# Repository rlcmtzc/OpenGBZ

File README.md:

&emsp;&emsp;&emsp;&emsp;&emsp;&emsp;&emsp;&emsp;&emsp;&emsp;&emsp;
# OpenGBZ
This is an **OpenSource Gameboy Zero PCB Project**. It is intended to make your own custom Button PCB and change the design to your wishes.  
Your welcome to download the PCB files and use it for your own project. If you change anything on the design it would be great if you  
push your changes here so the project can grow and we can get some nice different designs and ideas. Feel also free to push other gameboyzero related PCBs if you want to share them. 

Please also add your changes to the [forum](https://www.sudomod.com/forum/viewtopic.php?f=42&t=6499) post so everybody can easily see the changes and features of the different designs. I will also add the different designes here in the Readme file (Can´t update all the time and immediately so in the forum should be the newest versions and of course in the different directories)  

## How to add your Design and what is needed:
In the different directories you find the different PCBs. If you want to push a design please add a new directory with a name for your designe and in there add a README.md where you can shortly describe the features of your PCB.  

This readme should at least include (See OSDMG0v1 and OSDMG0v2 as a template) :
* **Your name** (and on which board its based of)
* If you tested the Board and if it works
* if you have also a BOM-file for the needed components
* if used in a Build you can link the Build
* A description of the Features of the Board (also some Pictures would be nice)
* Additional Info to the Board if needed. (For example a tutorial how to use specific non self-describing parts pf the boards or also provide software if needed)
* Short description on how to use the board and a list of parts needed for the Board (if not included in the BOM file)  

In the same directory as the readme you should add the .sch and .brd files and gerbers. (You can also link to your project if it was created with an online editor just make sure everybody can get the files)  

You can also add your current work in progress files and ask others for ideas or feedback. If so mark your post as work in progress.  

## Overview of currently added projects:
Here is a short overview of the currently added projets to this repository pleas keep in mind that this part is not necessary up to date pleas look in the forum post or in the different directories for the newest designs.  

| Directory Name       | Author Name           | Tested     | BOM-file | progress          |
| :-------------------:|:---------------------:| :---------:| :-------: | :----------------:|
| OSDMGBASE            | rlcmtzc12             | Yes        | not needed| finished          |
| OSDMG0v1             | rlcmtzc12             | Yes        | Yes       | finished          |
| OSDMG0v2             | rlcmtzc12             | No         | Yes       | finished          |
| GBPBASE by DerNuntius| DerNuntius            | Yes        | not needed| finished          |
| OSDMG_Leonardo_Shield| rlcmtzc12 (correia5022´s idea)| No         | not needed| finished          |
## Terms of use
* **You can do everything with the files the only thing I would appreciate is not to use the designs and sell the PCBs this should stay a non-profit project.**
* **Please add the logo found in this directory and add it to your PCB so everybody can determ that this is part of this project**
* **If your design bases of another designe please reference the author**
* **Be sure your files are availible and the readme is present**  

This Project should be for makers who want to create their own projects or just to test something new and this should be a help to getting started. If I see that the terms of use won´t be followed (especially the selling of boards) I´m forced to take down the project or to find another (not that open and easy) way to share the project.  

---  

Feel free to give me feedback/improvements (Best way to get in contact with me is over the [forum](https://www.sudomod.com/forum/memberlist.php?mode=viewprofile&u=9560) just leave a pm)  
Also I´m not a nativ english sepaker so be gracious :D  
I´m looking forward too see your designs

## License
Shield: [![CC BY-SA 4.0][cc-by-sa-shield]][cc-by-sa]

This work is licensed under a
[Creative Commons Attribution-NonCommercial-ShareAlike 4.0 International License][cc-by-sa].

[![CC BY-SA 4.0][cc-by-sa-image]][cc-by-sa]

[cc-by-sa]: https://creativecommons.org/licenses/by-nc-sa/4.0/
[cc-by-sa-image]: https://i.creativecommons.org/l/by-nc-sa/4.0/88x31.png
[cc-by-sa-shield]: https://img.shields.io/badge/License-CC%20BY--NC--SA%204.0-lightgrey.svg

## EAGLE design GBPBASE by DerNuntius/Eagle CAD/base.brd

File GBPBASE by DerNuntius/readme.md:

# First revision of the Gameboy Pocket PCB

**Author:** DerNuntius

**Tested:** No

**BOM-file:** unnecessary

**Build:** Later...

## Description:

It's a simple button PCB for the Gameboy Pocket. The PCB is perfect for projects with a Raspberry Pi or an Arduino to create an Arduboy clone.

## Get Project:
[Here](https://github.com/DerNuntius/Gameboy-Zero-Pocket-Button-PCB)

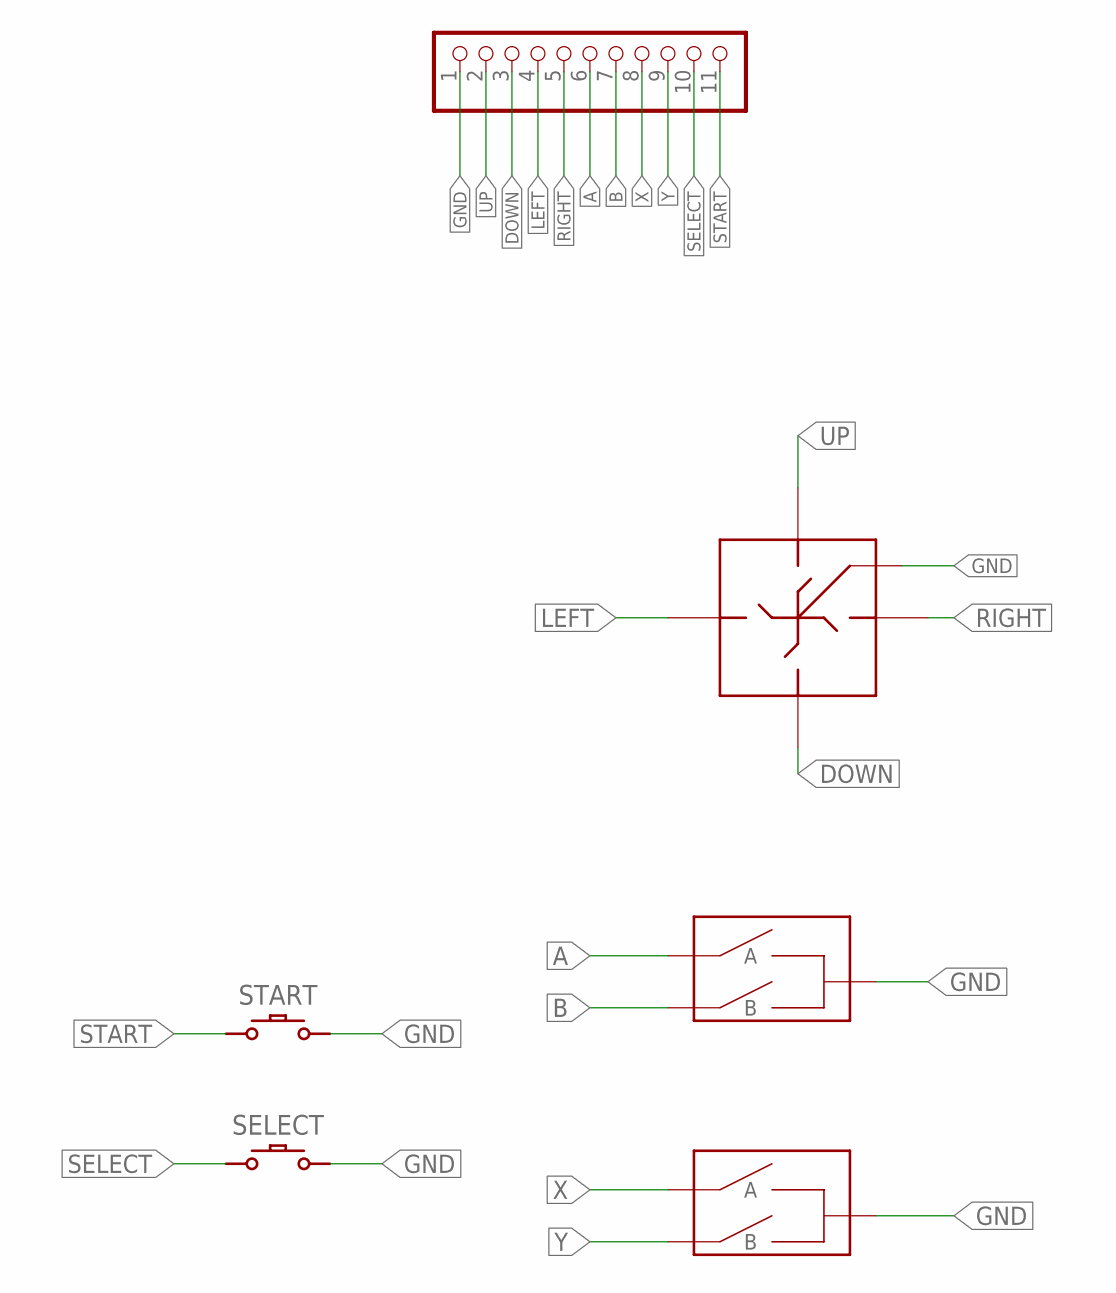
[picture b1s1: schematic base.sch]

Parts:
GND: PINHD-1X11_2.54; 1X11
S1: D-PAD
S2: XY_BUTTON; AB_BUTTON
S3: AB_BUTTON
SELECT: CONDUCTIVE_BUTTON_STARTSELECTCONDUCTIVE_BUTTON_TH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; CONDUCTIVE_BUTTON_THICK_STARTSELECT
START: CONDUCTIVE_BUTTON_STARTSELECTCONDUCTIVE_BUTTON_TH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; CONDUCTIVE_BUTTON_THICK_STARTSELECT

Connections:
A: GND.6, S3.A@1 (A), S3.A@2 (A)
B: GND.7, S3.B@1 (B), S3.B@2 (B)
DOWN: GND.3, S1.LEFT
GND: GND.1, S1.GND@1 (GND), S1.GND@2 (GND), S1.GND@3 (GND), S1.GND@4 (GND), S2.GND@1 (GND), S2.GND@2 (GND), S2.GND@3 (GND), S2.GND@4 (GND), S3.GND@1 (GND), S3.GND@2 (GND), S3.GND@3 (GND), S3.GND@4 (GND), SELECT.P$ACTIVE, SELECT.P$ACTIVE1 (P$ACTIVE), SELECT.P$ACTIVE2 (P$ACTIVE), SELECT.P$ACTIVE3 (P$ACTIVE), START.P$ACTIVE, START.P$ACTIVE1 (P$ACTIVE), START.P$ACTIVE2 (P$ACTIVE), START.P$ACTIVE3 (P$ACTIVE)
LEFT: GND.4, S1.UP
RIGHT: GND.5, S1.DOWN
SELECT: GND.10, SELECT.P$GND, SELECT.P$GND1 (P$GND), SELECT.P$GND2 (P$GND), SELECT.P$GND3 (P$GND)
START: GND.11, START.P$GND, START.P$GND1 (P$GND), START.P$GND2 (P$GND), START.P$GND3 (P$GND)
UP: GND.2, S1.RIGHT
X: GND.8, S2.A@1 (A), S2.A@2 (A)
Y: GND.9, S2.B@1 (B), S2.B@2 (B)

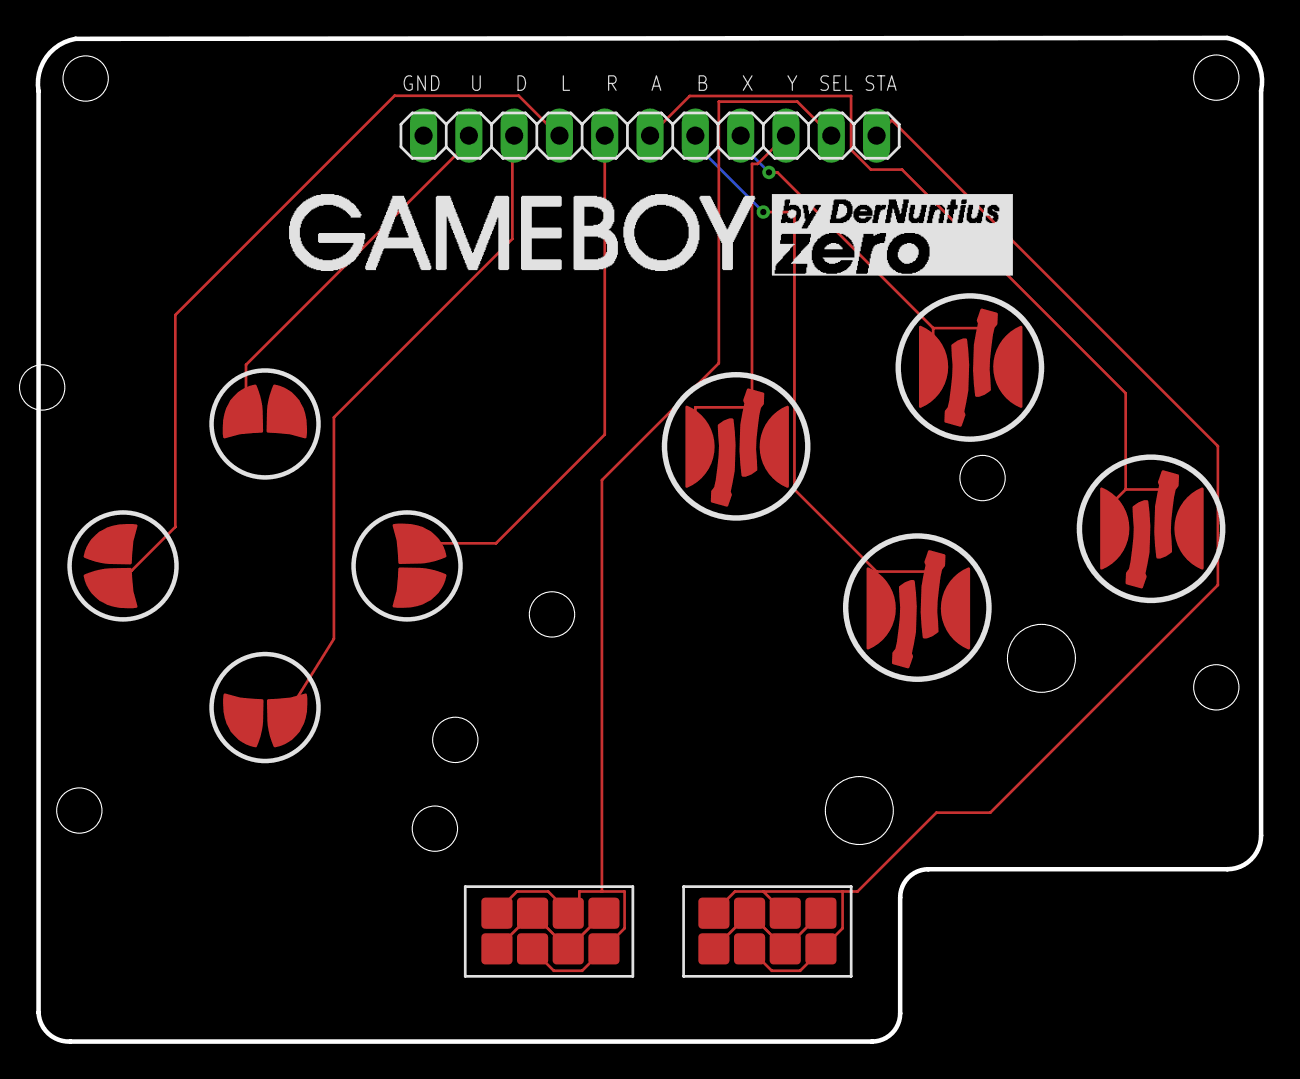
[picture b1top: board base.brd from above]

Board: 2 copper layers, 68.6 x 56.3 mm, 6 parts (0 on the bottom side), 11 nets.

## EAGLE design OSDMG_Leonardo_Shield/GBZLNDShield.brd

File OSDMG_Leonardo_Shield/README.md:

**Author:** rlcmtzc12 *(Based on correia5022 idea)*  
**Tested:** no  
**BOM-file:** not needed   
**Build:** /  

## Description:

This is a Shield like Projekt for the Leonardo/ Pro micro. There is place for a Pro Micro or Leonardo Board and a Battery input and a LED output. It can be also used the same liek the OSDMGBASE Board by just using the throughole pads (Bat and LED of course only works with an Arduino/Leonardo Board).
## Get Project:
The attached Eagle-files include everything.

## Images:

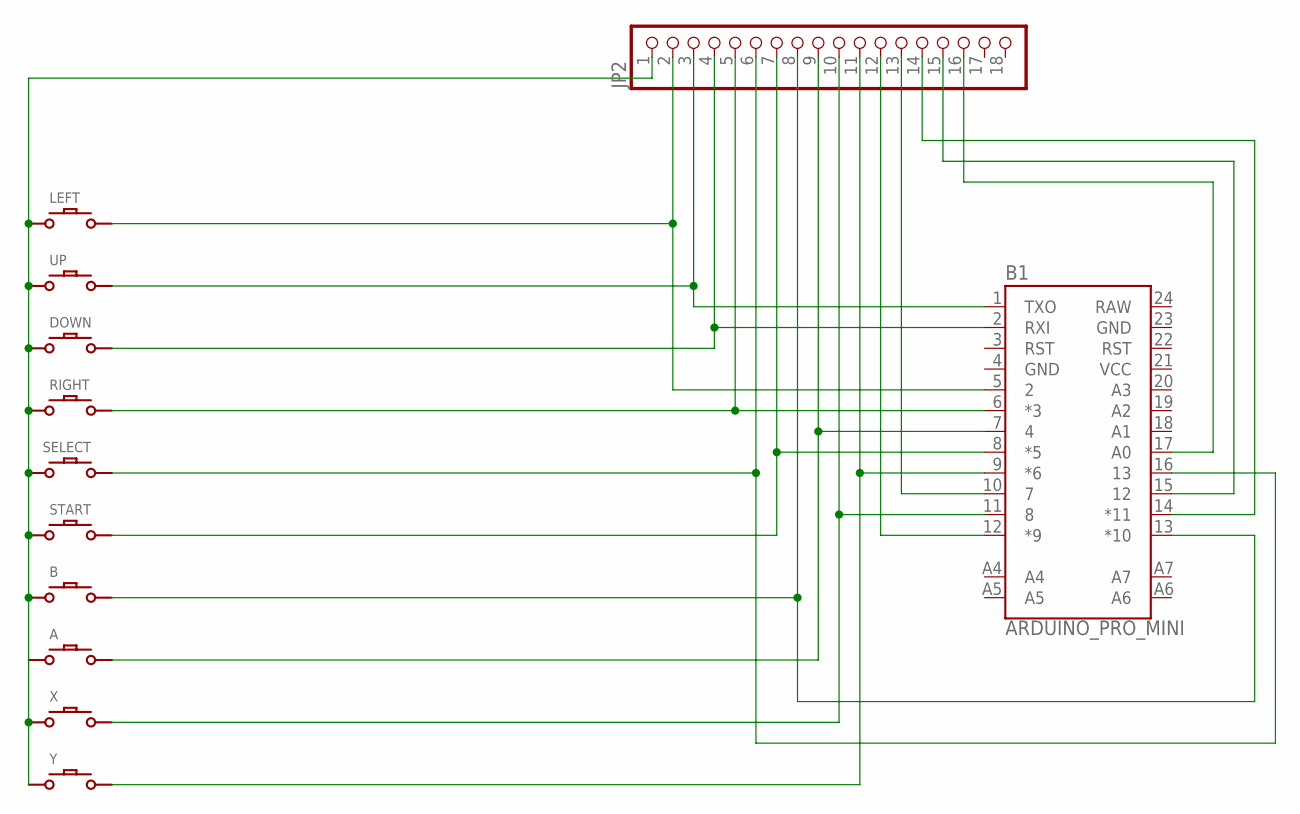
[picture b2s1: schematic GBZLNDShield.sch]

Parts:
A: DMG-BTN
B: DMG-BTN
B1: ARDUINO_PRO_MINI
DOWN: DMG-BTN
JP2: PINHD-1X18-BIG; 1X18-BIG
LEFT: DMG-BTN
RIGHT: DMG-BTN
SELECT: DMG-BTN; DMG-SEL
START: DMG-BTN; DMG-SEL
UP: DMG-BTN
X: DMG-BTN
Y: DMG-BTN

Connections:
GND: A.P$1, B.P$1, B1.4 (GND), B1.23 (GND), DOWN.P$1, JP2.1, LEFT.P$1, RIGHT.P$1, SELECT.P$2, START.P$2, UP.P$1, X.P$1, Y.P$1
unnamed: B1.5 (2), JP2.2, LEFT.P$2
unnamed: B1.1 (TXO), JP2.3, UP.P$2
unnamed: B1.2 (RXI), DOWN.P$2, JP2.4
unnamed: B1.6 (*3), JP2.5, RIGHT.P$2
unnamed: B1.16 (13), JP2.6, SELECT.P$1
unnamed: B1.12 (*9), JP2.12
unnamed: B.P$2, B1.13 (*10), JP2.8
unnamed: A.P$2, B1.7 (4), JP2.9
unnamed: B1.10 (7), JP2.13
unnamed: B1.14 (*11), JP2.14
unnamed: B1.8 (*5), JP2.7, START.P$1
unnamed: B1.9 (*6), JP2.11, Y.P$2
unnamed: B1.11 (8), JP2.10, X.P$2
unnamed: B1.15 (12), JP2.15
unnamed: B1.17 (A0), JP2.16
RAW: B1.24 (RAW)
VCC: B1.21 (VCC)

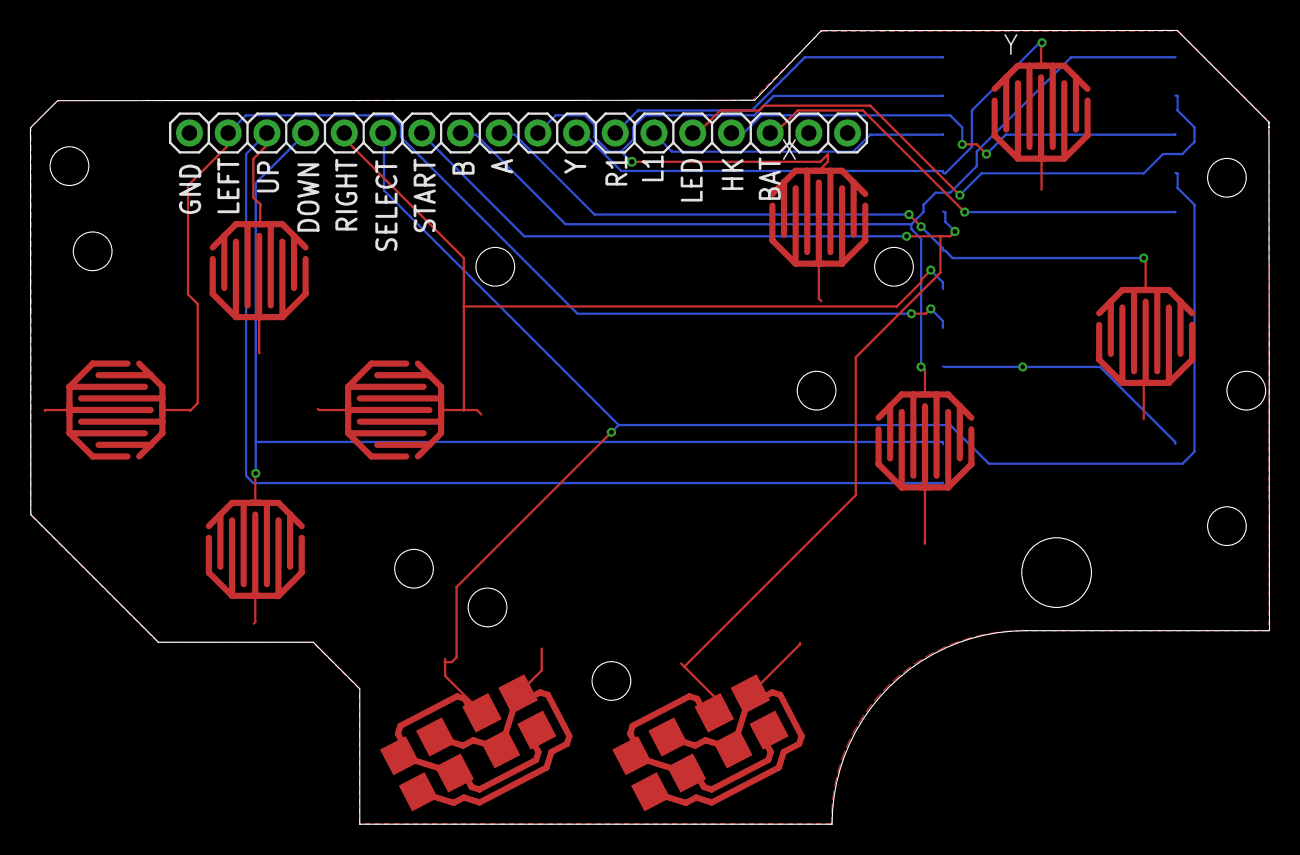
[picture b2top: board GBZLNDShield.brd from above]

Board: 2 copper layers, 81.3 x 52.1 mm, 12 parts (1 on the bottom side), 16 nets.

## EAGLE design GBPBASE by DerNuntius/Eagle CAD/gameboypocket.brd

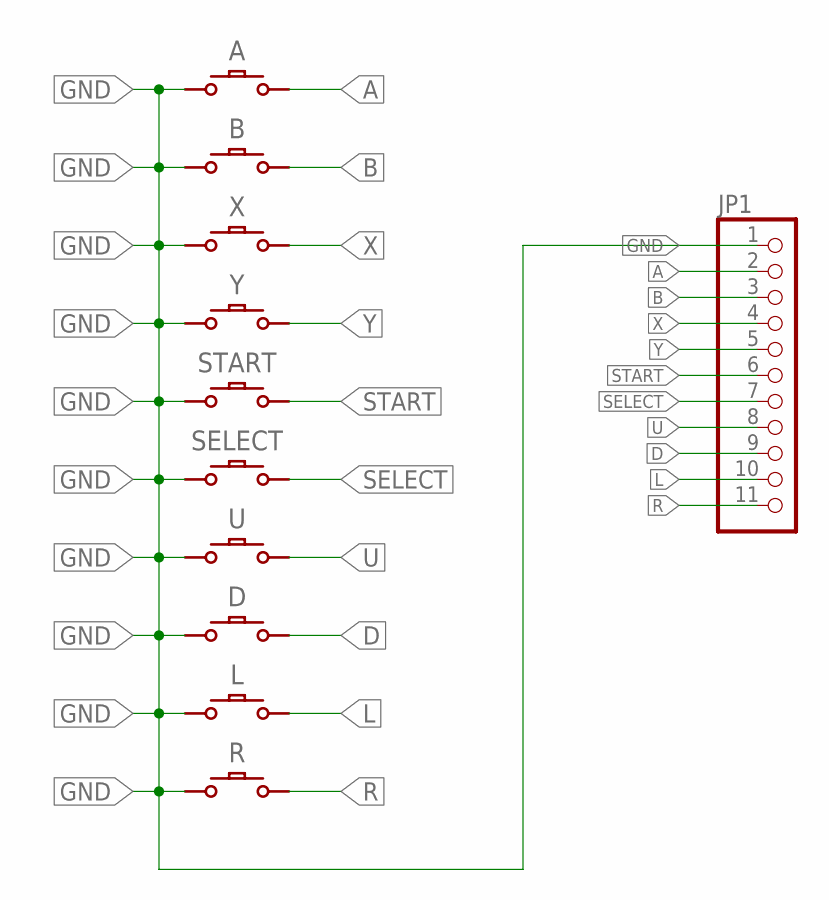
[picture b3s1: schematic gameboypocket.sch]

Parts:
A: CONDUCTIVE_BUTTON
B: CONDUCTIVE_BUTTON
D: CONDUCTIVE_BUTTON
JP1: PINHD-1X11; 1X11
L: CONDUCTIVE_BUTTON
R: CONDUCTIVE_BUTTON
SELECT: CONDUCTIVE_BUTTON_STARTSELECT
START: CONDUCTIVE_BUTTON_STARTSELECT
U: CONDUCTIVE_BUTTON
X: CONDUCTIVE_BUTTON_DRILL
Y: CONDUCTIVE_BUTTON_DRILL

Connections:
A: A.P$ACTIVE, JP1.2
B: B.P$ACTIVE, JP1.3
D: D.P$ACTIVE, JP1.9
GND: A.P$GND, B.P$GND, D.P$GND, JP1.1, L.P$GND, R.P$GND, SELECT.P$GND, START.P$GND, U.P$GND, X.P$GND, Y.P$GND
L: JP1.10, L.P$ACTIVE
R: JP1.11, R.P$ACTIVE
SELECT: JP1.7, SELECT.P$ACTIVE
START: JP1.6, START.P$ACTIVE
U: JP1.8, U.P$ACTIVE
X: JP1.4, X.P$ACTIVE
Y: JP1.5, Y.P$ACTIVE

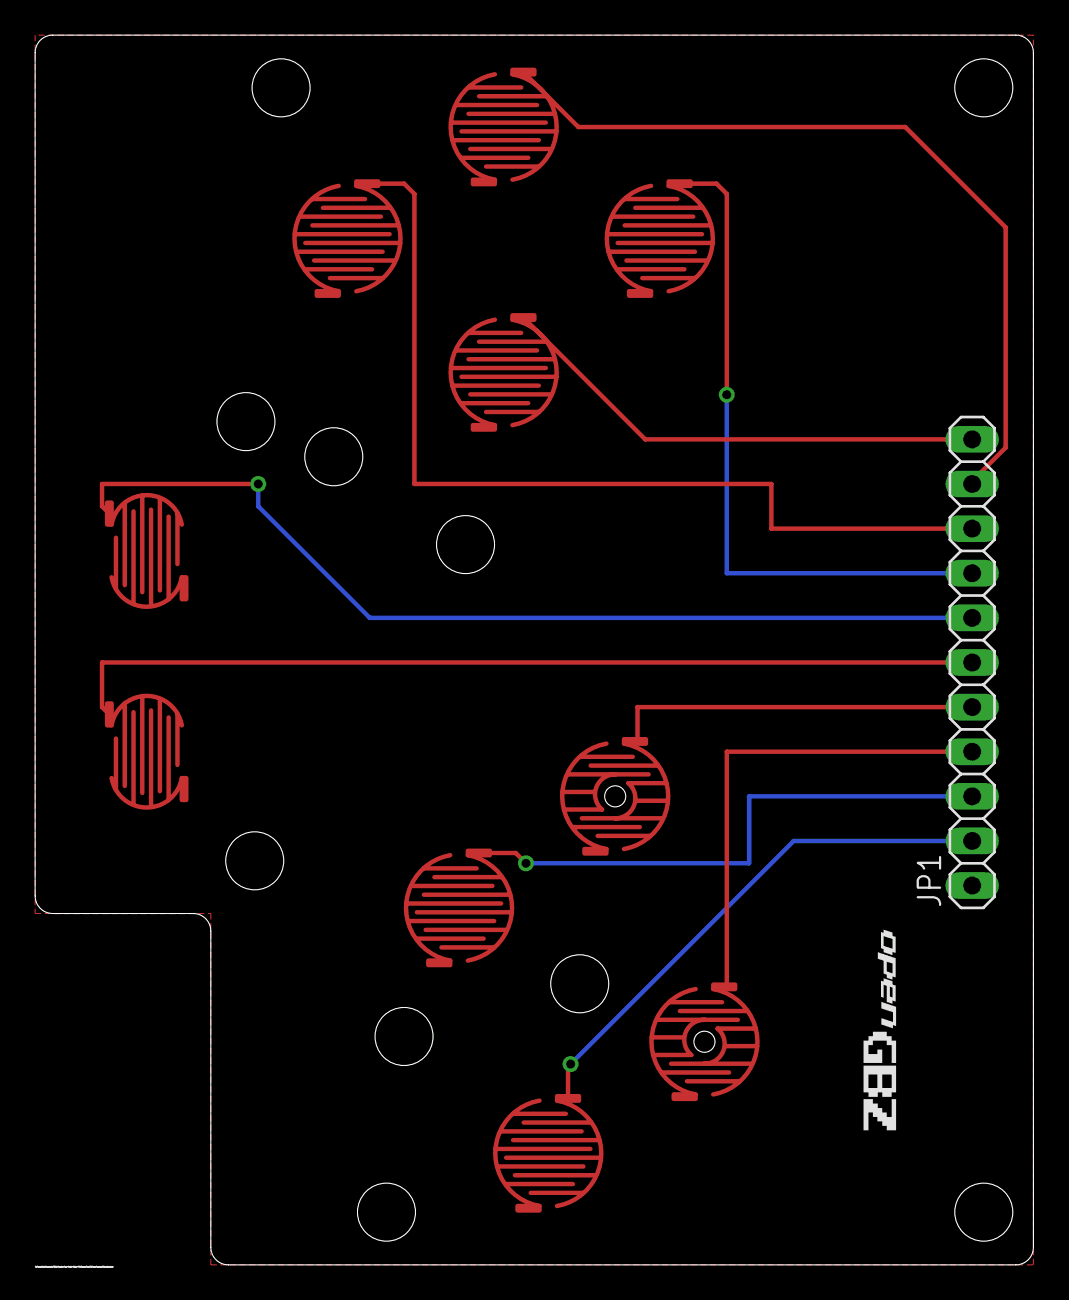
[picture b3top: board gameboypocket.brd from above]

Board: 2 copper layers, 56.8 x 70.0 mm, 21 parts (0 on the bottom side), 11 nets.

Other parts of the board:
U$3, U$4, U$5, U$6, U$7, U$8, U$9, U$10, U$11, U$12: STAND-OFF

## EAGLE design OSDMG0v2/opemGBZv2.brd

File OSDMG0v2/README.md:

# Second Version of my opensource DMG Board

**Author:** rlcmtzc12 *(Based on rlcmtzc12 design)*  
**Tested:** Not yet  
**BOM-file:** Not yet   
**Build:** /  

## Description:

This board has an integrated charging and Boost circuit. The Boost circuit is based on the TPS61236P Boost IC. (Datasheed found [here](http://www.ti.com/lit/ds/symlink/tps61236p.pdf)) The outputvoltage is set to around 5 Volt. The Boost circuit can be switched on with a powerswitch. The charging circuit of the Battery is based on TP4056 IC which can charge a single lithium-ion battery with up to 1A (Datasheed found [here](https://www.e-gizmo.net/oc/kits%20documents/TP4056-1A%20Li-ion%20Battery%20Charger/TP4056-1A%20Li-ion%20battery%20charger%20Manual.pdf)). Also I integrated the FS312G-F IC which protect the Battery from overcharge, overdischarge and overcurrent (Datasheed found [here](https://www.ic-fortune.com/upload/Download/FS312F-G-DS-12_EN.pdf)). The board will be charged with an usb type c connector. On the board is place for an standard PAM module which then connect to place for a volumewheel and the aux-port. On the front there are the standard buttons (Up, Down, Left, Right, Start, Select, A, B, X, Y) All the Buttons are connected with an ATmega32u4. The Atmega32u4 can be programmed over the USB-C Port by switching a Button. The Code for the Arduino can be used from the [sudomod wiki](https://www.sudomod.com/wiki/index.php/Leonardo_/_Pro_Micro).
The difference to the first version is that this one has an integrated safe shutdown which is completely done on the hardwareside so you don´t need any script.
It works like following:  
First when you switch on the power a capacitor gets charged. When the capacitor is charged over a given treshold voltage a Mosfet switches on and allow voltage to the pi the capacitor charges on to 5V.
The capacitor is charged in a few miliseconds so there is no delay to turn the raspberry pi on. Next when you turn the switch off a transistor turns an pin to ground this pin is connected to the reset pin of
the pi so when this pin is set to ground the pi turns off. At the same time the capasitor slowly discharges over an resistor when the capacitor is under the thresholdvoltage the Mosfet turns off and so cut the power to the pi.
From turn off until the Mosfet cuts the power pass 15s with this resistor, this is enough time that the pi can shutdown. You also can change the Time by increasing/decreasing the resistor size/ capacitor size. So you only have to
connect a wire to the reset pin off the pi for this safeshutdown to work.

Some Simulationdata of the Boost IC:  
  
(Keep in mind there is also heat, a lot of heat at 4A so you probably should not use it over 3A. I try to make the copperareas on the PCB quit big so they can work as heat sinks but of course they will not dissipate 5V@4A --> 20W)

Here are the Schematics. I splitted them in Eagle up for better overview:

The finished PCB (The nameplacement could be done better):

## Get Project:
Just download the Eagle files.

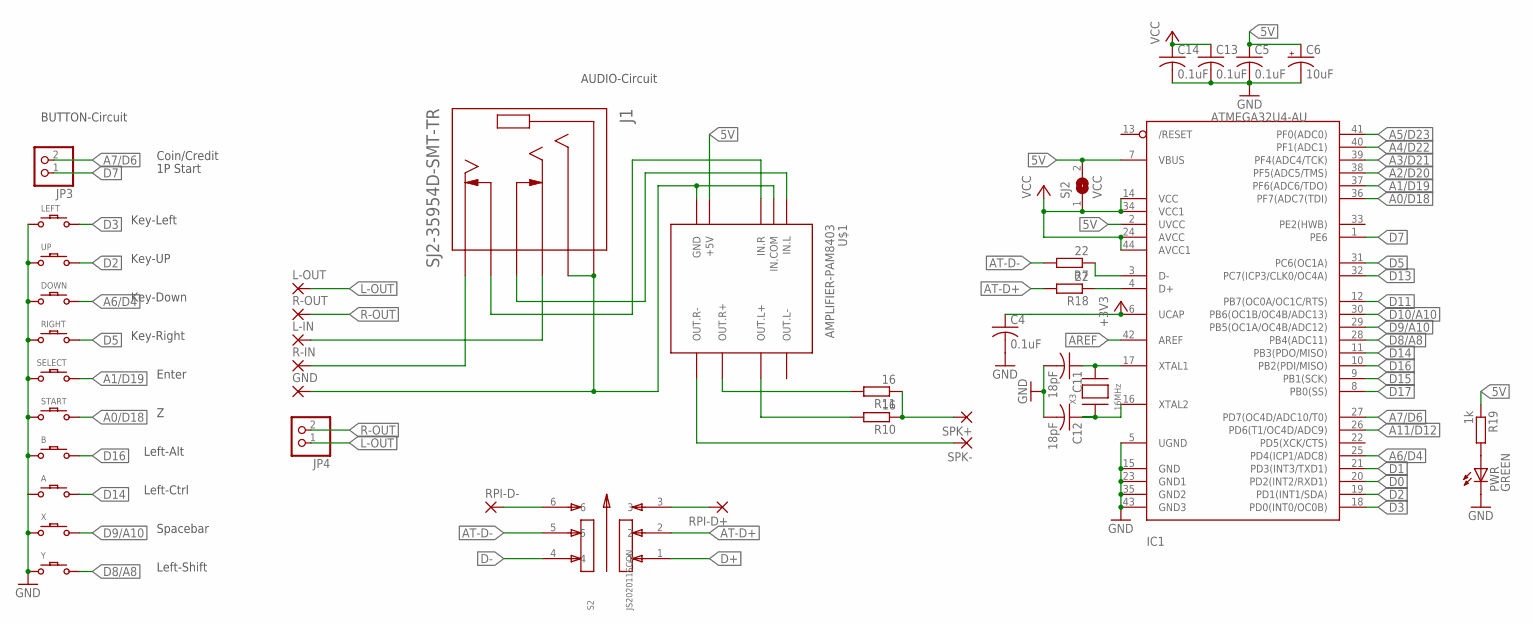
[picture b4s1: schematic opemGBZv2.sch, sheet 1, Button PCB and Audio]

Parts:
A: DMG-BTN
B: DMG-BTN
C4, C5, C13, C14: 0.1uF; C0805K
C6: 10uF; A/3216-18R
C11, C12: 18pF; C0805K
DOWN: DMG-BTN
GND: WIREPADSMD1,27-254; SMD1,27-2,54
IC1: ATMEGA32U4-AU; TQFP44
J1: SJ2-35954D-SMT-TR; CUI_SJ2-35954D-SMT-TR
JP3, JP4: PINHD-1X2; 1X02
L-IN: WIREPADSMD1,27-254; SMD1,27-2,54
L-OUT: WIREPADSMD1,27-254; SMD1,27-2,54
LEFT: DMG-BTN
PWR: GREEN; CHIPLED_0805
R7, R18: 22; R0603
R10, R11: 16; R0603
R19: 1k; R0603
R-IN: WIREPADSMD1,27-254; SMD1,27-2,54
R-OUT: WIREPADSMD1,27-254; SMD1,27-2,54
RIGHT: DMG-BTN
RPI-D+: WIREPADSMD1,27-254; SMD1,27-2,54
RPI-D-: WIREPADSMD1,27-254; SMD1,27-2,54
S2: JS202011SCQN; SW_JS202011SCQN
SELECT: DMG-BTN; DMG-SEL
SJ2: VCC; SJ
SPK+: WIREPADSMD1,27-254; SMD1,27-2,54
SPK-: WIREPADSMD1,27-254; SMD1,27-2,54
START: DMG-BTN; DMG-SEL
U$1: AMPLIFIER-PAM8403
UP: DMG-BTN
X: DMG-BTN
X3: 16MHz; NX5032
Y: DMG-BTN

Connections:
5V: C5.1, C6.+, IC1.2 (UVCC), IC1.7 (VBUS), R19.1, SJ2.2, U$1.+5V; also elsewhere on the board
+3V3: C4.1, IC1.6 (UCAP)
A0/D18: IC1.36 (PF7(ADC7(TDI)), START.P$1
A1/D19: IC1.37 (PF6(ADC6/TDO)), SELECT.P$1
A2/D20: IC1.38 (PF5(ADC5/TMS))
A3/D21: IC1.39 (PF4(ADC4/TCK))
A4/D22: IC1.40 (PF1(ADC1))
A5/D23: IC1.41 (PF0(ADC0))
A6/D4: DOWN.P$2, IC1.25 (PD4(ICP1/ADC8))
A7/D6: IC1.27 (PD7(OC4D/ADC10/T0)), JP3.2
A11/D12: IC1.26 (PD6(T1/OC4D/ADC9))
AREF: IC1.42 (AREF)
AT-D+: R18.2, S2.2
AT-D-: R7.2, S2.5
D0: IC1.20 (PD2(INT2/RXD1))
D1: IC1.21 (PD3(INT3/TXD1))
D2: IC1.19 (PD1(INT1/SDA)), UP.P$2
D3: IC1.18 (PD0(INT0/OC0B)), LEFT.P$2
D5: IC1.31 (PC6(OC1A)), RIGHT.P$2
D7: IC1.1 (PE6), JP3.1
D8/A8: IC1.28 (PB4(ADC11)), Y.P$2
D9/A10: IC1.29 (PB5(OC1A/OC4B/ADC12)), X.P$2
D10/A10: IC1.30 (PB6(OC1B/OC4B/ADC13))
D11: IC1.12 (PB7(OC0A/OC1C/RTS))
D13: IC1.32 (PC7(ICP3/CLK0/OC4A))
D14: A.P$2, IC1.11 (PB3(PDO/MISO))
D15: IC1.9 (PB1(SCK))
D16: B.P$2, IC1.10 (PB2(PDI/MISO))
D17: IC1.8 (PB0(SS))
D+: S2.1; also elsewhere on the board
D-: S2.4; also elsewhere on the board
GND: A.P$1, B.P$1, C4.2, C5.2, C6.-, C11.2, C12.2, C13.2, C14.2, DOWN.P$1, IC1.5 (UGND), IC1.15 (GND), IC1.23 (GND1), IC1.35 (GND2), IC1.43 (GND3), LEFT.P$1, PWR.C, RIGHT.P$1, SELECT.P$2, START.P$2, UP.P$1, X.P$1, Y.P$1; also elsewhere on the board
L-OUT: JP4.1, L-OUT.1
unnamed: RPI-D-.1, S2.6
unnamed: RPI-D+.1, S2.3
unnamed: R11.2, U$1.OUT.R+
unnamed: GND.1, J1.1 (SLEEVE), J1.4 (RING2), U$1.GND, U$1.IN.COM
unnamed: J1.11 (RING1_SWITCH), U$1.IN.L
unnamed: J1.10 (TIP_SWITCH), U$1.IN.R
unnamed: J1.2 (TIP), R-IN.1
unnamed: J1.3 (RING1), L-IN.1
unnamed: R10.2, U$1.OUT.L+
unnamed: R10.1, R11.1, SPK+.1
unnamed: SPK-.1, U$1.OUT.R-
unnamed: IC1.3 (D-), R7.1
unnamed: IC1.4 (D+), R18.1
unnamed: C12.1, IC1.16 (XTAL2), X3.P$1
unnamed: C11.1, IC1.17 (XTAL1), X3.P$2
unnamed: PWR.A, R19.2
R-OUT: JP4.2, R-OUT.1
VCC: C13.1, C14.1, IC1.14 (VCC), IC1.24 (AVCC), IC1.34 (VCC1), IC1.44 (AVCC1), SJ2.1; also elsewhere on the board

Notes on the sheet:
AUDIO-Circuit
BUTTON-Circuit
Key-UP
Key-Left
Key-Down
Key-Right
Left-Ctrl
Left-Alt
Spacebar
Left-Shift
Enter
Coin/Credit
1P Start

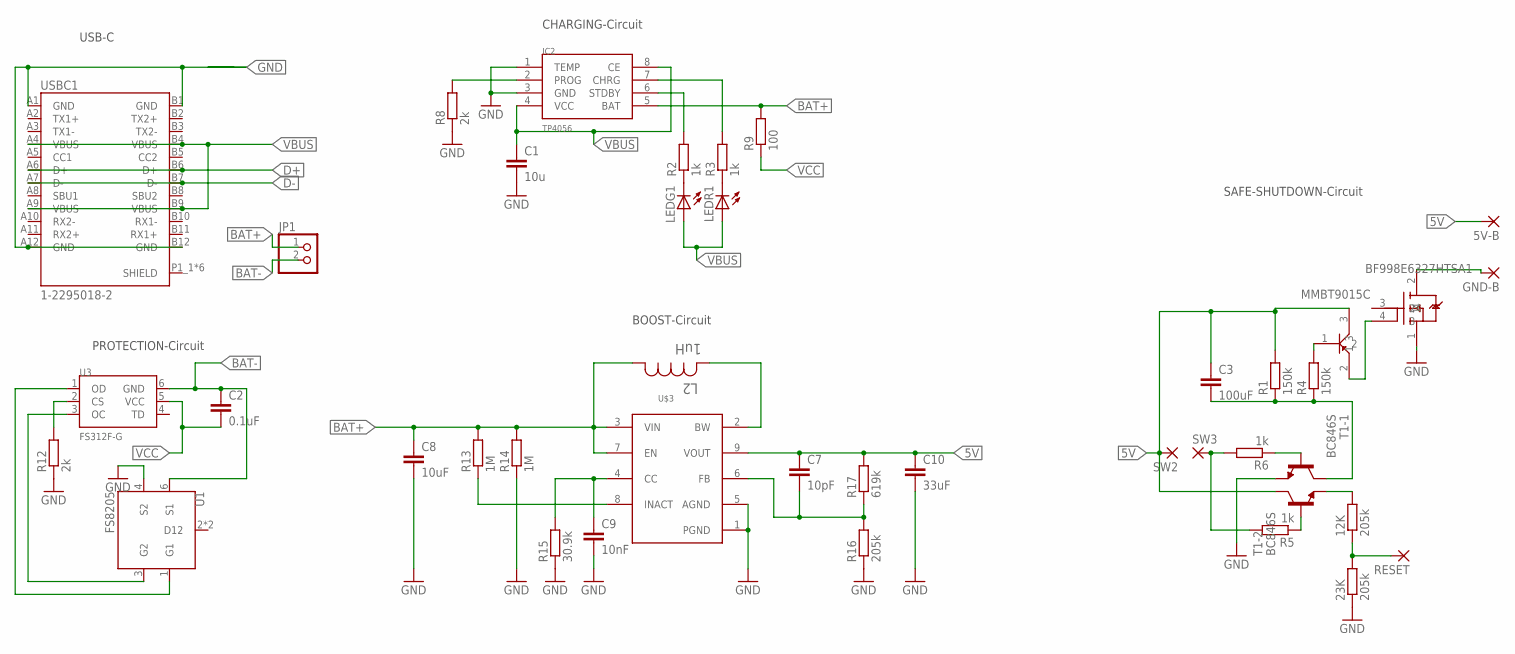
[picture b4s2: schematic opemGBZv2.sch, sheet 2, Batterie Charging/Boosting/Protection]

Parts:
5V-B: WIREPADSMD1,27-254; SMD1,27-2,54
12K, 23K: 205k; R0603
BF998E6327HTSA1: INF-SOT143-4-1_V_1; INF-SOT143-4-1_V_1PRIMARY
C1: 10u; C0603
C2: 0.1uF; C0603
C3: 100uF; C1812
C7: 10pF; C1812
C8: 10uF; C1812
C9: 10nF; C1812
C10: 33uF; C1812
GND-B: WIREPADSMD1,27-254; SMD1,27-2,54
IC2: TP4056; SOP-8
JP1: PINHD-1X2; 1X02
L2: 1uH; INDM7676X435N
LEDG1: LEDCHIP-LED0603; CHIP-LED0603
LEDR1: LEDCHIP-LED0603; CHIP-LED0603
MMBT9015C: INF-SOT23_M_1; INF-SOT23_M_1PRIMARY
R1, R4: 150k; R0603
R2, R3, R5, R6: 1k; R0603
R8, R12: 2k; R0603
R9: 100; R0603
R13, R14: 1M; R0603
R15: 30.9k; R0603
R16: 205k; R0603
R17: 619k; R0603
RESET: WIREPADSMD1,27-254; SMD1,27-2,54
SW2, SW3: WIREPADSMD1,27-254; SMD1,27-2,54
T1: BC846S; SOT363
U1: FS8205; SOT23-6
U3: FS312F-G; SOT23-6
U$3: TPS61235RWLR; CONV_TPS61235RWLR
USBC1: 1-2295018-2; TE_1-2295018-2

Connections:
5V: 5V-B.1, C3.1, C7.1, C10.1, MMBT9015C.3 (1), R1.2, R17.2, SW2.1, T1.3 (C), U$3.9 (VOUT); also elsewhere on the board
BAT+: C8.1, IC2.5 (BAT), JP1.1, L2.1, R9.2, R13.2, R14.2, U$3.3 (VIN), U$3.7 (EN)
BAT-: C2.1, JP1.2, U1.6 (S1), U3.6 (GND)
D+: USBC1.A6 (D+), USBC1.B6 (D+); also elsewhere on the board
D-: USBC1.A7 (D-), USBC1.B7 (D-); also elsewhere on the board
GND: 23K.1, BF998E6327HTSA1.1 (4), C1.2, C8.2, C9.2, C10.2, IC2.1 (TEMP), IC2.3 (GND), R8.1, R12.1, R14.1, R15.1, R16.1, T1.1 (E), U1.4 (S2), U$3.1 (PGND), U$3.5 (AGND), USBC1.A1 (GND), USBC1.A12 (GND), USBC1.B1 (GND), USBC1.B12 (GND); also elsewhere on the board
unnamed: BF998E6327HTSA1.2 (1), GND-B.1
unnamed: BF998E6327HTSA1.4 (3), MMBT9015C.2 (3)
unnamed: MMBT9015C.1 (2), R4.2
unnamed: 12K.2, T1.4 (E)
unnamed: C3.2, R1.1, R4.1, T1.6 (C)
unnamed: R6.1, T1.2 (B)
unnamed: R5.2, R6.2, SW3.1
unnamed: R5.1, T1.5 (B)
unnamed: R13.1, U$3.8 (INACT)
unnamed: C9.1, R15.2, U$3.4 (CC)
unnamed: IC2.6 (STDBY), R2.2
unnamed: IC2.7 (CHRG), R3.2
unnamed: LEDG1.C, R2.1
unnamed: L2.2, U$3.2 (BW)
unnamed: LEDR1.C, R3.1
unnamed: C7.2, R16.2, R17.1, U$3.6 (FB)
unnamed: IC2.2 (PROG), R8.2
unnamed: U1.3 (G2), U3.3 (OC)
unnamed: U1.1 (G1), U3.1 (OD)
unnamed: R12.2, U3.2 (CS)
unnamed: 12K.1, 23K.2, RESET.1
VBUS: C1.1, IC2.4 (VCC), IC2.8 (CE), LEDG1.A, LEDR1.A, USBC1.A4 (VBUS), USBC1.A9 (VBUS), USBC1.B4 (VBUS), USBC1.B9 (VBUS)
VCC: C2.2, R9.1, U3.5 (VCC); also elsewhere on the board

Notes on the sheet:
BOOST-Circuit
PROTECTION-Circuit
CHARGING-Circuit
SAFE-SHUTDOWN-Circuit
USB-C

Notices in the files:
parts and their libraries:
SparkFun-Electromechanical: Licensing: CC v3.0 Share-Alike You are welcome to use this library for commercial purposes.
diy-modules: Released under the Creative Commons Attribution 4.0 International License: http://creativecommons.org/licenses/by/4.0
